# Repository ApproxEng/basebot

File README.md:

BaseBot
=======

Basebot is a set of laser cut templates, hardware recommendations and guides and software for a cheap wheeled robotics platform.

Get the SVG or DXF files for the acrylic parts from this repository, and see the wiki for [the bill of materials](http://basebot.org/w/index.php?title=Bill_of_Materials) and [assembly instructions](http://basebot.org/w/index.php?title=Assembly_Instructions) - these don't currently include control or power circuitry, but you'll end up with a solid chassis including motors ready for your controller of choice...

The latest version (v16) looks like this (lacking any form of control circuitry!)

This has evolved quite a bit from an earlier version (v4 or so)

Developed at Makespace in Cambridge, UK (http://www.makespace.org)

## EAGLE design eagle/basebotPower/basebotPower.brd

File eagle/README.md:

Files for BaseBot circuit boards. At the moment this consists solely of the very simple power distribution board; this simplifies connection of the battery, power switches and servos to whatever control board you're using but doesn't do anything particularly clever.

Any Eagle files here must be kept sufficiently simple that they can be opened with the no-cost version of Eagle!

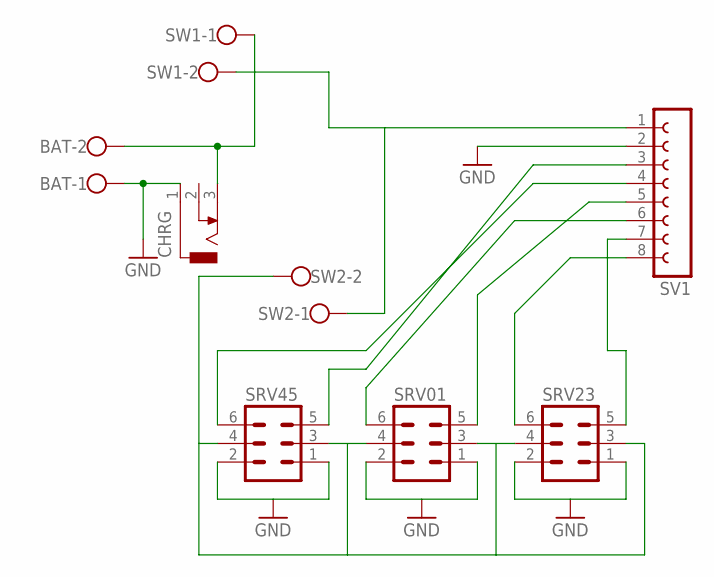
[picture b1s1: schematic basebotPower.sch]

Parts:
BAT: W237-102
CHRG: DCJ0303
SRV01, SRV23, SRV45: MA03-2
SV1: FE08-1; FE08
SW1, SW2: W237-102

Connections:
GND: BAT.1, CHRG.1, SRV01.1, SRV01.2, SRV23.1, SRV23.2, SRV45.1, SRV45.2, SV1.2
unnamed: BAT.2, CHRG.3, SW1.1
unnamed: SRV23.6, SV1.8
unnamed: SRV23.5, SV1.7
unnamed: SRV45.6, SV1.4
unnamed: SRV45.5, SV1.3
unnamed: SRV01.6, SV1.6
unnamed: SRV01.5, SV1.5
unnamed: SRV01.3, SRV01.4, SRV23.3, SRV23.4, SRV45.3, SRV45.4, SW2.2
SERVOPWR: SV1.1, SW1.2, SW2.1

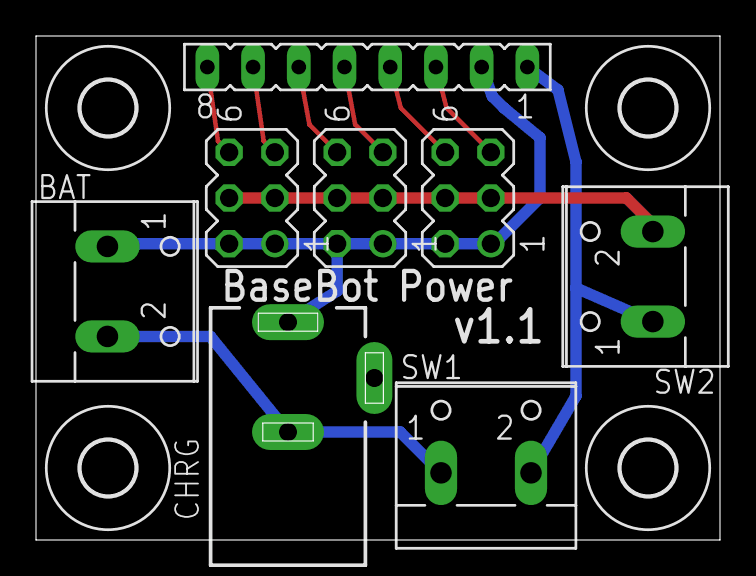
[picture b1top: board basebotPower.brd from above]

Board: 2 copper layers, 38.0 x 28.0 mm, 12 parts (0 on the bottom side), 10 nets.

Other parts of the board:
U$1, U$2, U$3, U$4: 3,0

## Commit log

2013-10-22 Added SVG and (some) DXF files for the current version of the basebot
2013-10-28 Updated files to new version for 6v batteries and battery pack. Added appropriate bits and pieces for the accessory kits!
2013-11-20 Updated platters and wheel designs
2013-11-22 Added refined version with rounded cornered tabs, extra width for slots etc.
2013-11-22 Expanded slots for motor mounts, some half hearted attempt at page layout.
2014-01-25 Updated to switch to 30mm verticals
2014-01-25 Updated design to latest, including optional fitting for optical encoders on the wheels, expanded options for verticals and refactoring to 30mm uprights.
2014-01-26 Moved risers to 10mm wide to fit on grid spacing, fixed issue with encoder LED mount part colliding with wheel position tuner piece.
2014-02-04 Updated with new pattern designed around using a prop adapter (4mm to 6mm) to anchor the wheels. Still untested!
2014-02-06 Added more platters (optional) as well as re-instating the extra diagonal slot. Still can't actually be used if the H-bridge is in place but if not it's available again now.
2014-05-29 Added motor mounts based on continuous rotation servos
2014-05-29 Updated chassis to reflect change to cr servos, should fit better (but servo horn mount not tested yet). Added binding to centre point, and provided alternative front panel with mount for servo drive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
2014-05-29 Added arduino sketch from science centre demo
2014-06-05 Updated wheel design, added servo cable slots, made centre piece modular, removed side-slots from servo mounts (will require filing of servos, but cleaner)
2014-06-06 Added my (probably broken) attempt at using Eagle to generate a power distribution board.
2014-06-12 Board layout done, sent to OSHPark for fabrication! Will presumably find out whether it's actually correct at some point when they arrive.
2014-06-13 Fixed stupid error in board involving the wrong wiring for the servos, also changed the layout to use screw terminals rather than on board switches, this allows for panel mount (and higher current) s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
2014-06-18 Tweaks to layout, allow for variable distance between servo and edge of platter to accomodate the futuba servos (slightly smaller)
2014-07-10 Updated layout with options for dropped servo mounts to accomodate castors
2014-07-10 Added tripod layout files and dxf layer files for transparent and opaque layers. Trial to test castor, tripod and variable spacing for servos.
2014-07-10 Stupid typos...
2014-07-15 Fixed slot alignment in tripod layout along with wheel servo horn fittings. Still need to a) increase inner wheel hold diameter, and b) add curved front to the tripod layout as the current arrangemen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
2014-07-15 Updated layout, fixed a few bugs and added logos. Added cross markers to top plates and extended front plate to be more useful.
2014-07-15 Added tripod layout for A3 sheet including accessories
2014-07-22 Fixes slot lengths back to 10mm, the laser kerf already provides more than enough leeway and there's no variation there like there is for thickness.
2014-09-03 Removed old layout file, was overly confusing. Added the start of an alternative to the top and bottom platters to allow a 6xAA battery pack to be accessed from below, not tested yet though.
2014-09-03 Removed old parts.svg files, migrated accessories into a distinct file. Still need to re-do the accessory vertical elements so we can make use of the same verticals as used by the core, a simple chan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
2014-09-03 Added DXF files for the version of the basebot seen at EMF2014
2014-09-03 Update LICENSE
2014-09-05 Added logo
2014-09-24 Updated platter layout to allow for deeper servos (such as the turnigy 4309/4303 from hobbyking) and for a 6AA battery holder accessible from underneath the robot. Added reinforcement, not sure how e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
2014-10-15 Widened whole layout somewhat to accommodate reinforcing around battery compartment. Improved general fittings.
2014-10-15 Updated to include random missing holes (oops...)
2014-10-16 Fixed too-narrow battery holder, as well as a few other tweaks to increase the amount of room for servos.
2014-10-30 Added insert to allow the wires from the battery holder to clear the entrance port more easily.
